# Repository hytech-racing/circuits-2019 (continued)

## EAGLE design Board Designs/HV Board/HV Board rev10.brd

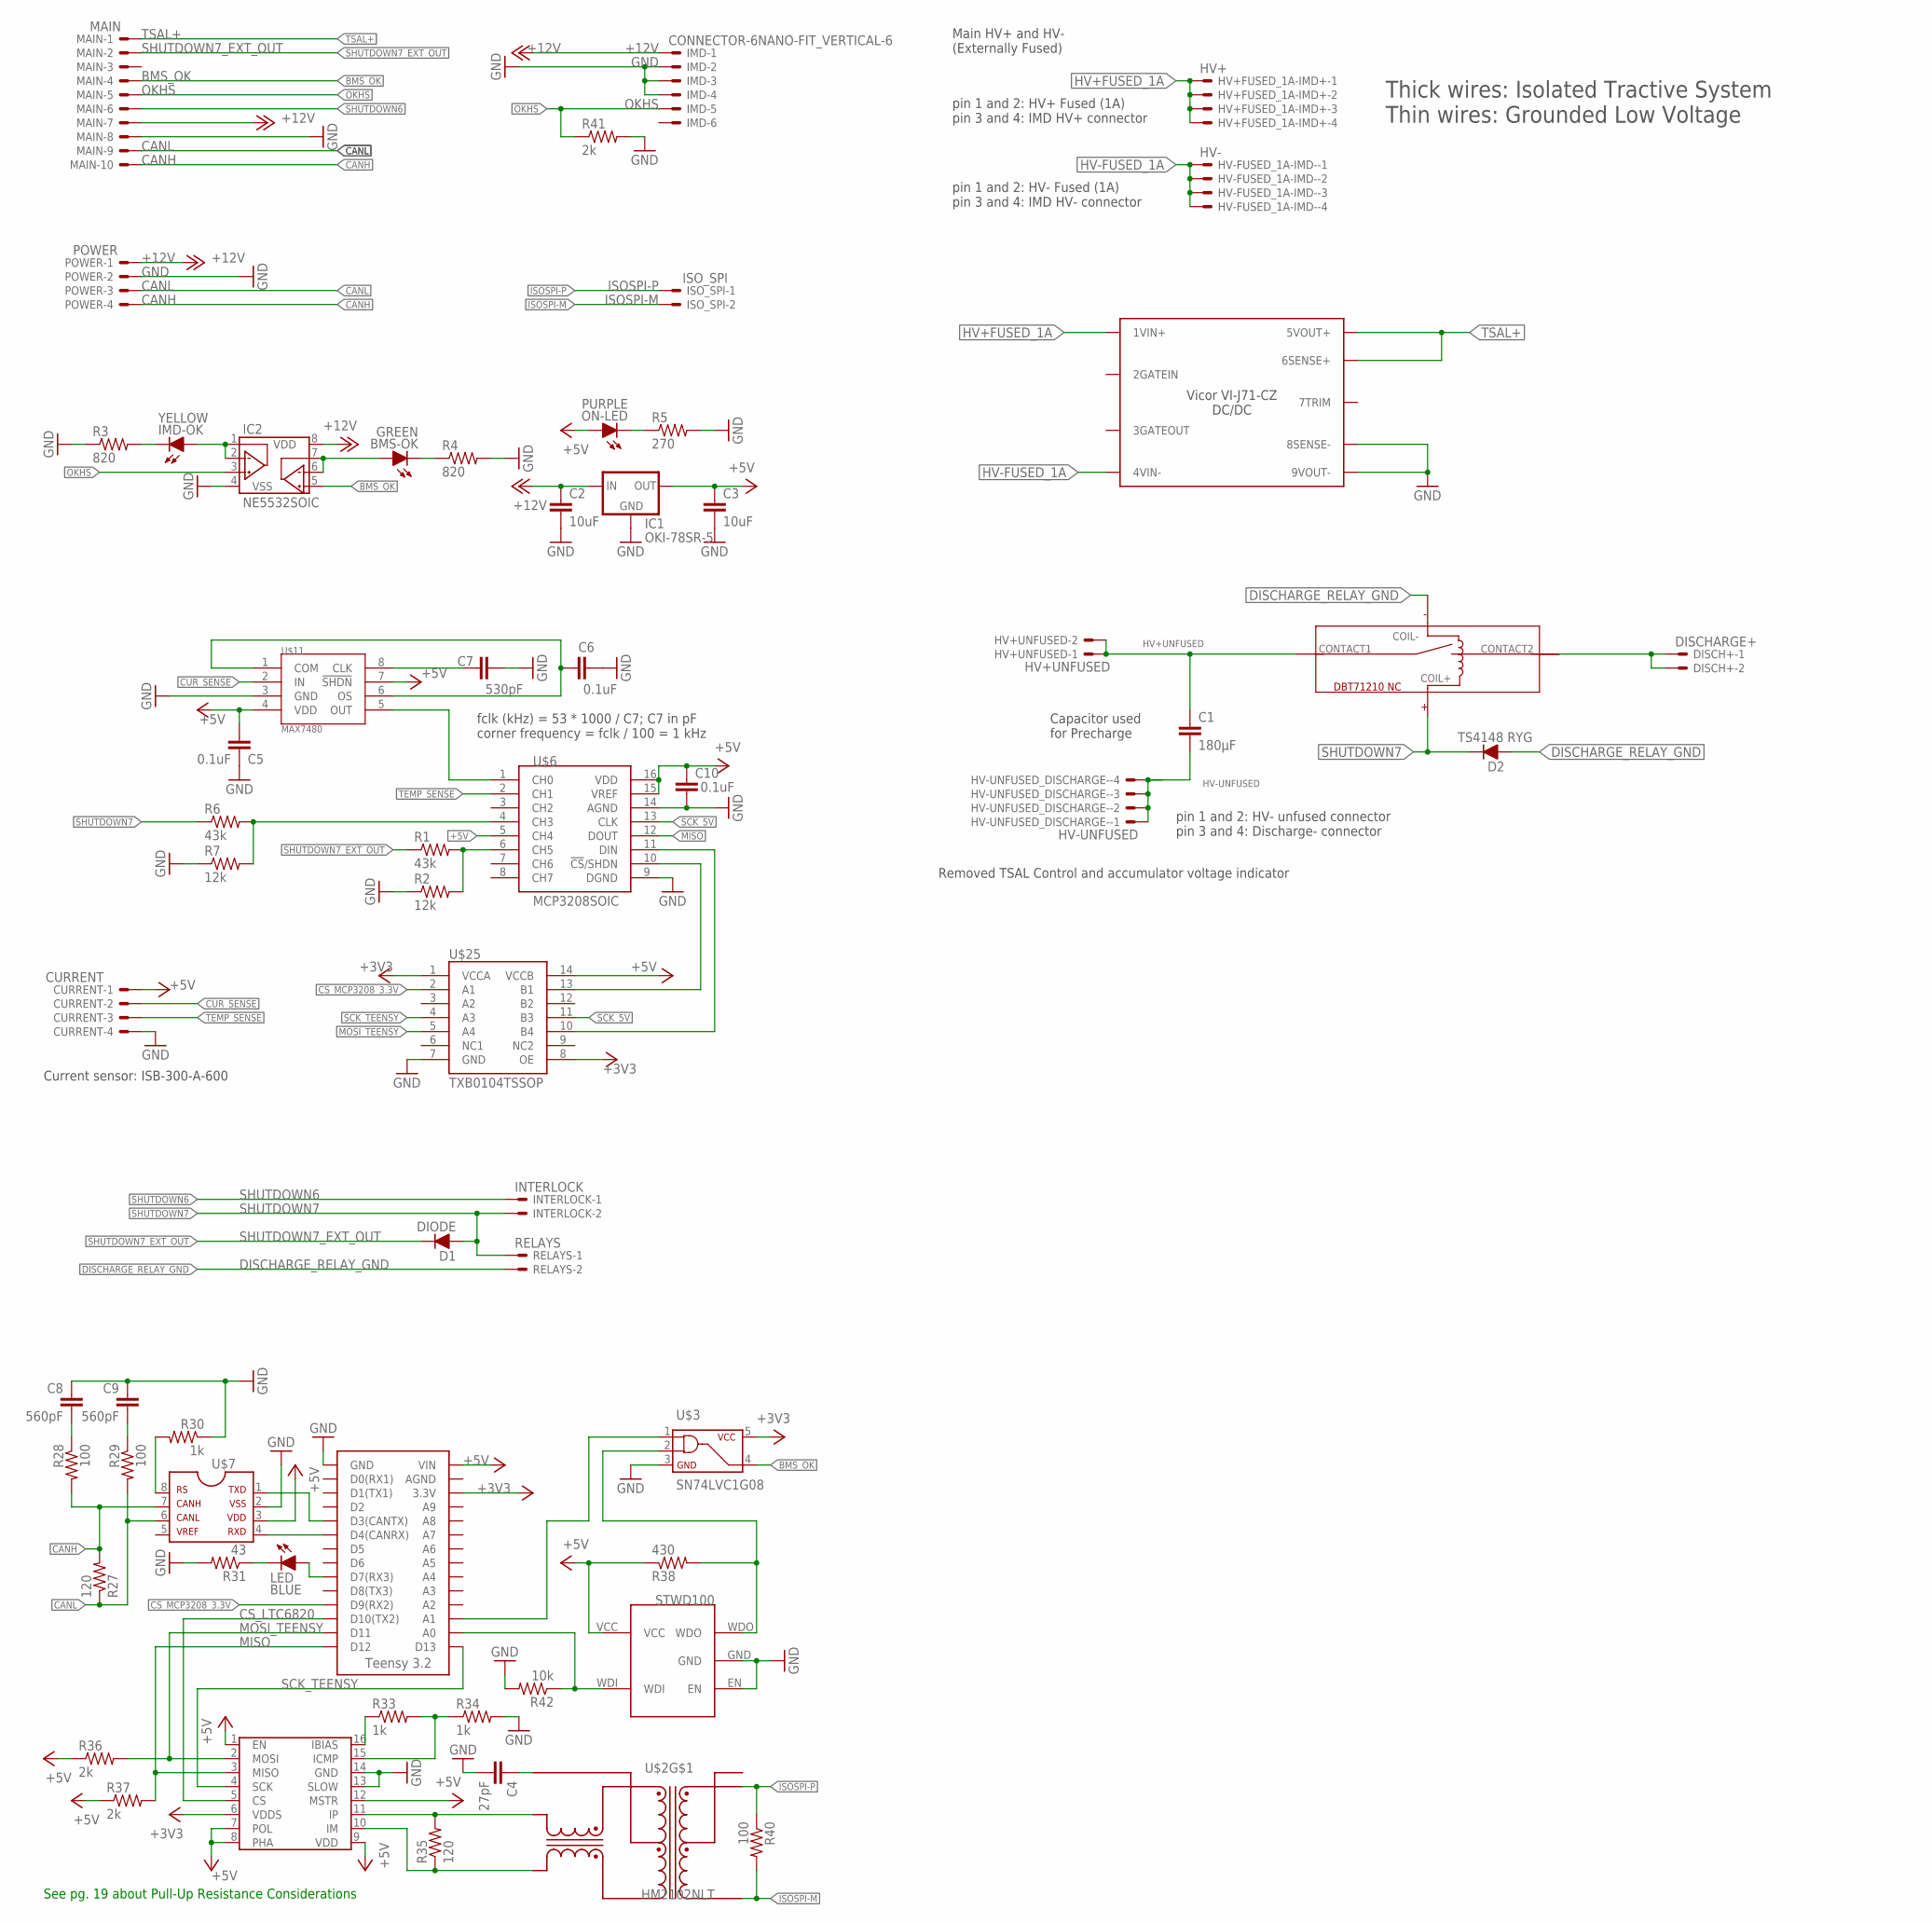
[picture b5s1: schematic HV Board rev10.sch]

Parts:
BMS-OK: GREEN; LED-805
C1: 180µF; LLS2V221MELZ
C2, C3: 10uF; 0805
C4: 27pF; 0805
C5, C6, C10: 0.1uF; 0805
C7: 530pF; 0805
C8, C9: 560pF; 0805
CURRENT: CURRENT; NANO-FIT_VERTICAL-4
D1: DIODE; DO-41
D2: TS4148 RYG; 0805_D
DISCH+: DISCHARGE+; NANO-FIT_VERTICAL-2
HV+FUSED_1A-IMD+: HV+; NANO-FIT_VERTICAL-4
HV+UNFUSED: HV+UNFUSED; NANO-FIT_VERTICAL-2
HV-FUSED_1A-IMD-: HV-; NANO-FIT_VERTICAL-4
HV-UNFUSED_DISCHARGE-: HV-UNFUSED; NANO-FIT_VERTICAL-4
IC1: OKI-78SR-5; OKI-78SR
IC2: NE5532SOIC; SOIC-08
IMD: CONNECTOR-6NANO-FIT_VERTICAL-6; NANO-FIT_VERTICAL-6
IMD-OK: YELLOW; LED-805
INTERLOCK: INTERLOCK; NANO-FIT_VERTICAL-2
ISO_SPI: ISO_SPI; NANO-FIT_VERTICAL-2
LED: BLUE; LED-805
MAIN: MAIN; NANO-FIT_VERTICAL-10
ON-LED: PURPLE; LED-805
POWER: POWER; NANO-FIT_VERTICAL-4
R1, R6: 43k; 0805
R2, R7: 12k; 0805
R3, R4: 820; 0805
R5: 270; 0805
R27, R35: 120; 0805
R28, R29, R40: 100; 0805
R30, R33, R34: 1k; 0805
R31: 43; 0805
R36, R37, R41: 2k; 0805
R38: 430; 0805
R42: 10k; 0805
RELAYS: RELAYS; NANO-FIT_VERTICAL-2
U$2: HM2102NLT
U$3: SN74LVC1G08; SOT-23-5
U$4: DBT71210
U$5: HV_DCDC_VI-J71-CZ
U$6: MCP3208SOIC; SOIC-16
U$7: MCP2551; SOIC-08
U$8: LTC6820; MSOP-16
U$9: TEENSY_3.2_SIMPLE
U$10: STWD100; SOT23-5
U$11: MAX7480; SOIC-08
U$25: TXB0104TSSOP; TSSOP-14

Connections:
+3V3: U$3.5, U$8.6 (VDDS), U$9.3.3V, U$25.1 (VCCA), U$25.8 (OE)
+5V: C3.1, C5.1, C10.1, CURRENT.P$1, IC1.3 (OUT), ON-LED.A, R36.1, R37.1, R38.1, U$6.5 (CH4), U$6.15 (VREF), U$6.16 (VDD), U$7.3, U$8.1 (EN), U$8.7 (POL), U$8.8 (PHA), U$8.9 (VDD), U$8.12 (MSTR), U$9.VIN, U$10.VCC, U$11.4 (VDD), U$25.14 (VCCB)
+12V: C2.1, IC1.1 (IN), IC2.8 (VDD), IMD.P$1, MAIN.P$7, POWER.P$1
BMS_OK: IC2.5 (VINB+), MAIN.P$4, U$3.4
CANH: MAIN.P$10, POWER.P$4, R27.2, R28.2, U$7.7
CANL: MAIN.P$9, POWER.P$3, R27.1, R29.2, U$7.6
CS_LTC6820: U$8.5 (CS), U$9.D10(TX2)
CS_MCP3208_3.3V: U$9.D9(RX2), U$25.2 (A1)
CUR_SENSE: CURRENT.P$2, U$11.2 (IN)
DISCHARGE_RELAY_GND: D2.A, RELAYS.P$2, U$4.COIL-
GND: C2.2, C3.2, C4.2, C5.2, C6.2, C7.2, C8.1, C9.1, C10.2, CURRENT.P$4, IC1.2 (GND), IC2.4 (VSS), IMD.P$2, IMD.P$3, IMD.P$4, MAIN.P$8, POWER.P$2, R2.1, R3.1, R4.2, R5.2, R7.1, R30.1, R31.2, R34.2, R41.2, R42.2, U$3.3, U$5.8SENSE-, U$5.9VOUT-, U$6.9 (DGND), U$6.14 (AGND), U$7.2, U$8.13 (SLOW), U$8.14 (GND), U$9.GND, U$10.EN, U$10.GND, U$11.3 (GND), U$25.7 (GND)
HV+FUSED_1A: HV+FUSED_1A-IMD+.P$1, HV+FUSED_1A-IMD+.P$2, HV+FUSED_1A-IMD+.P$3, HV+FUSED_1A-IMD+.P$4, U$5.1VIN+
HV+UNFUSED: C1.P$1 (1), HV+UNFUSED.P$1, HV+UNFUSED.P$2, U$4.CONTACT1
HV+UNFUSED_FSAE_DISCHARGE: DISCH+.P$1, DISCH+.P$2, U$4.CONTACT2
HV-FUSED_1A: HV-FUSED_1A-IMD-.P$1, HV-FUSED_1A-IMD-.P$2, HV-FUSED_1A-IMD-.P$3, HV-FUSED_1A-IMD-.P$4, U$5.4VIN-
HV-UNFUSED: C1.P$2 (2), HV-UNFUSED_DISCHARGE-.P$1, HV-UNFUSED_DISCHARGE-.P$2, HV-UNFUSED_DISCHARGE-.P$3, HV-UNFUSED_DISCHARGE-.P$4
IM: R35.1, U$2.P$10 (TD-), U$8.10 (IM)
IP: R35.2, U$2.P$12 (TD+), U$8.11 (IP)
ISOSPI-M: ISO_SPI.P$2, R40.2, U$2.P$3 (MX-)
ISOSPI-P: ISO_SPI.P$1, R40.1, U$2.P$1 (MX+)
MISO: R37.2, U$6.12 (DOUT), U$8.3 (MISO), U$9.D12
MOSI_5V: U$6.11 (DIN), U$25.10 (B4)
MOSI_TEENSY: R36.2, U$8.2 (MOSI), U$9.D11, U$25.5 (A4)
unnamed: U$6.1 (CH0), U$11.5 (OUT)
unnamed: C6.1, U$11.1 (COM), U$11.6 (OS)
unnamed: ON-LED.C, R5.1
unnamed: C7.1, U$11.8 (CLK)
unnamed: U$6.10 (!CS!/SHDN), U$25.13 (B1)
unnamed: R6.2, R7.2, U$6.4 (CH3)
unnamed: R1.2, R2.2, U$6.6 (CH5)
unnamed: U$7.1, U$9.D3(CANTX)
unnamed: R30.2, U$7.8
unnamed: C8.2, R28.1
unnamed: C9.2, R29.1
unnamed: LED.C, R31.1
unnamed: R33.1, U$8.16 (IBIAS)
unnamed: R33.2, R34.1, U$8.15 (ICMP)
unnamed: C4.1, U$2.P$11 (TCT)
unnamed: U$7.4, U$9.D4(CANRX)
unnamed: LED.A, U$9.D7(RX3)
unnamed: R38.2, U$3.2, U$10.WDO
unnamed: U$3.1, U$9.A1
unnamed: IC2.1 (VOUTA), IC2.2 (VINA-), IMD-OK.A
unnamed: BMS-OK.A, IC2.6 (VINB-), IC2.7 (VOUTB)
unnamed: BMS-OK.C, R4.1
unnamed: IMD-OK.C, R3.2
unnamed: R42.1, U$9.A0, U$10.WDI
OKHS: IC2.3 (VINA+), IMD.P$5, MAIN.P$5, R41.1
SCK_5V: U$6.13 (CLK), U$25.11 (B3)
SCK_TEENSY: U$8.4 (SCK), U$9.D13, U$25.4 (A3)
SHUTDOWN6: INTERLOCK.P$1, MAIN.P$6
SHUTDOWN7: D1.A, D2.C, INTERLOCK.P$2, R6.1, RELAYS.P$1, U$4.COIL+
SHUTDOWN7_EXT_OUT: D1.C, MAIN.P$2, R1.1
TEMP_SENSE: CURRENT.P$3, U$6.2 (CH1)
TSAL+: MAIN.P$1, U$5.5VOUT+, U$5.6SENSE+

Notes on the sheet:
Current sensor: ISB-300-A-600
Main HV+ and HV- (Externally Fused)
Thick wires: Isolated Tractive System Thin wires: Grounded Low Voltage
See pg. 19 about Pull-Up Resistance Considerations
Capacitor used for Precharge
Removed TSAL Control and accumulator voltage indicator
pin 1 and 2: HV+ Fused (1A) pin 3 and 4: IMD HV+ connector
pin 1 and 2: HV- Fused (1A) pin 3 and 4: IMD HV- connector
pin 1 and 2: HV- unfused connector pin 3 and 4: Discharge- connector
fclk (kHz) = 53 * 1000 / C7; C7 in pF corner frequency = fclk / 100 = 1 kHz

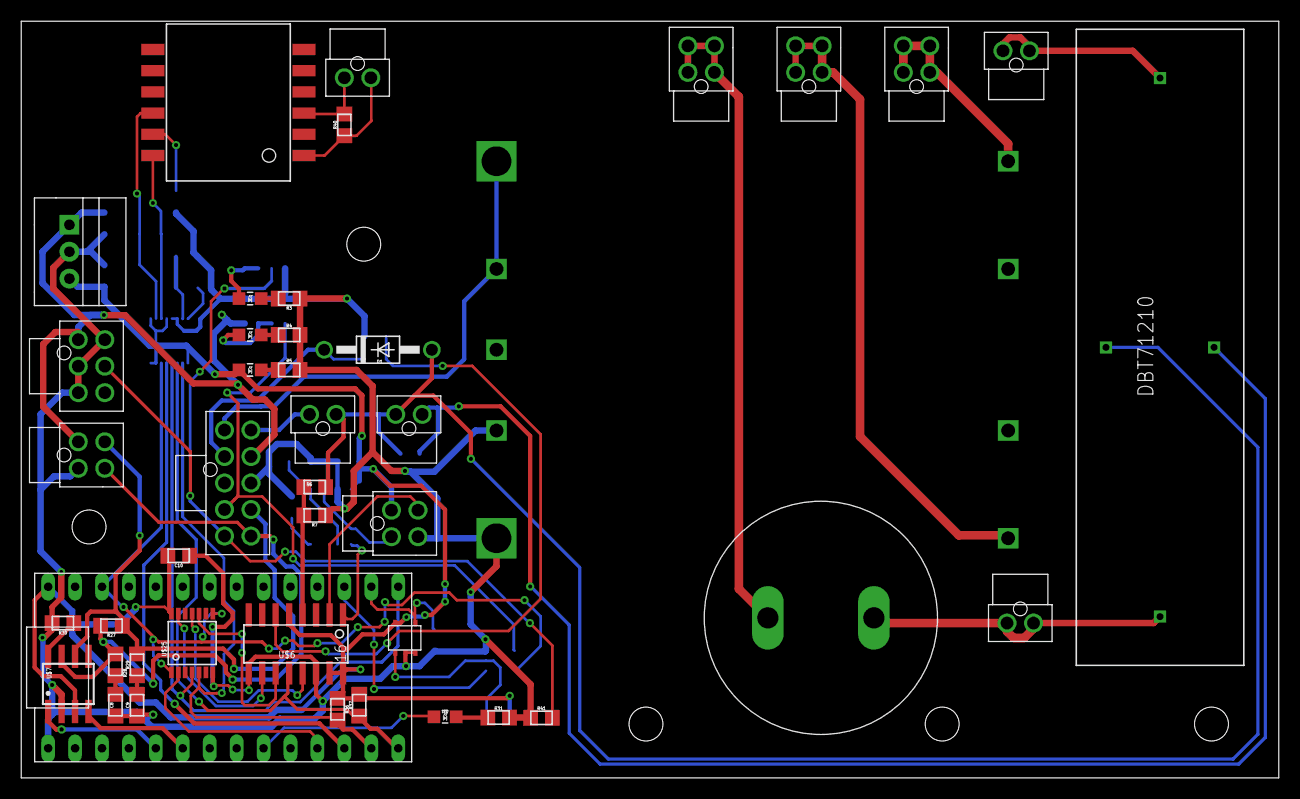
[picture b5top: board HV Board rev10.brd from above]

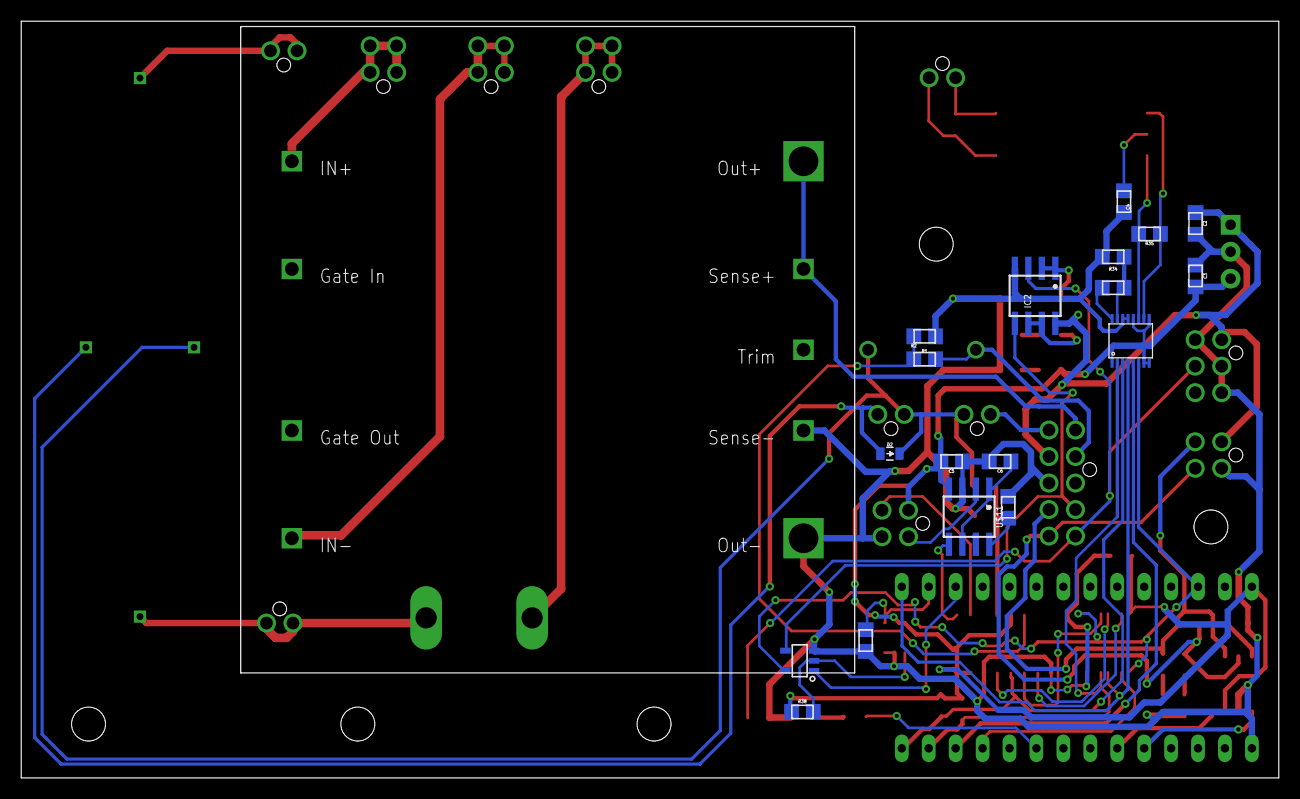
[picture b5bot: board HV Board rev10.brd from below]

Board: 2 copper layers, 118.6 x 71.4 mm, 62 parts (19 on the bottom side), 55 nets.

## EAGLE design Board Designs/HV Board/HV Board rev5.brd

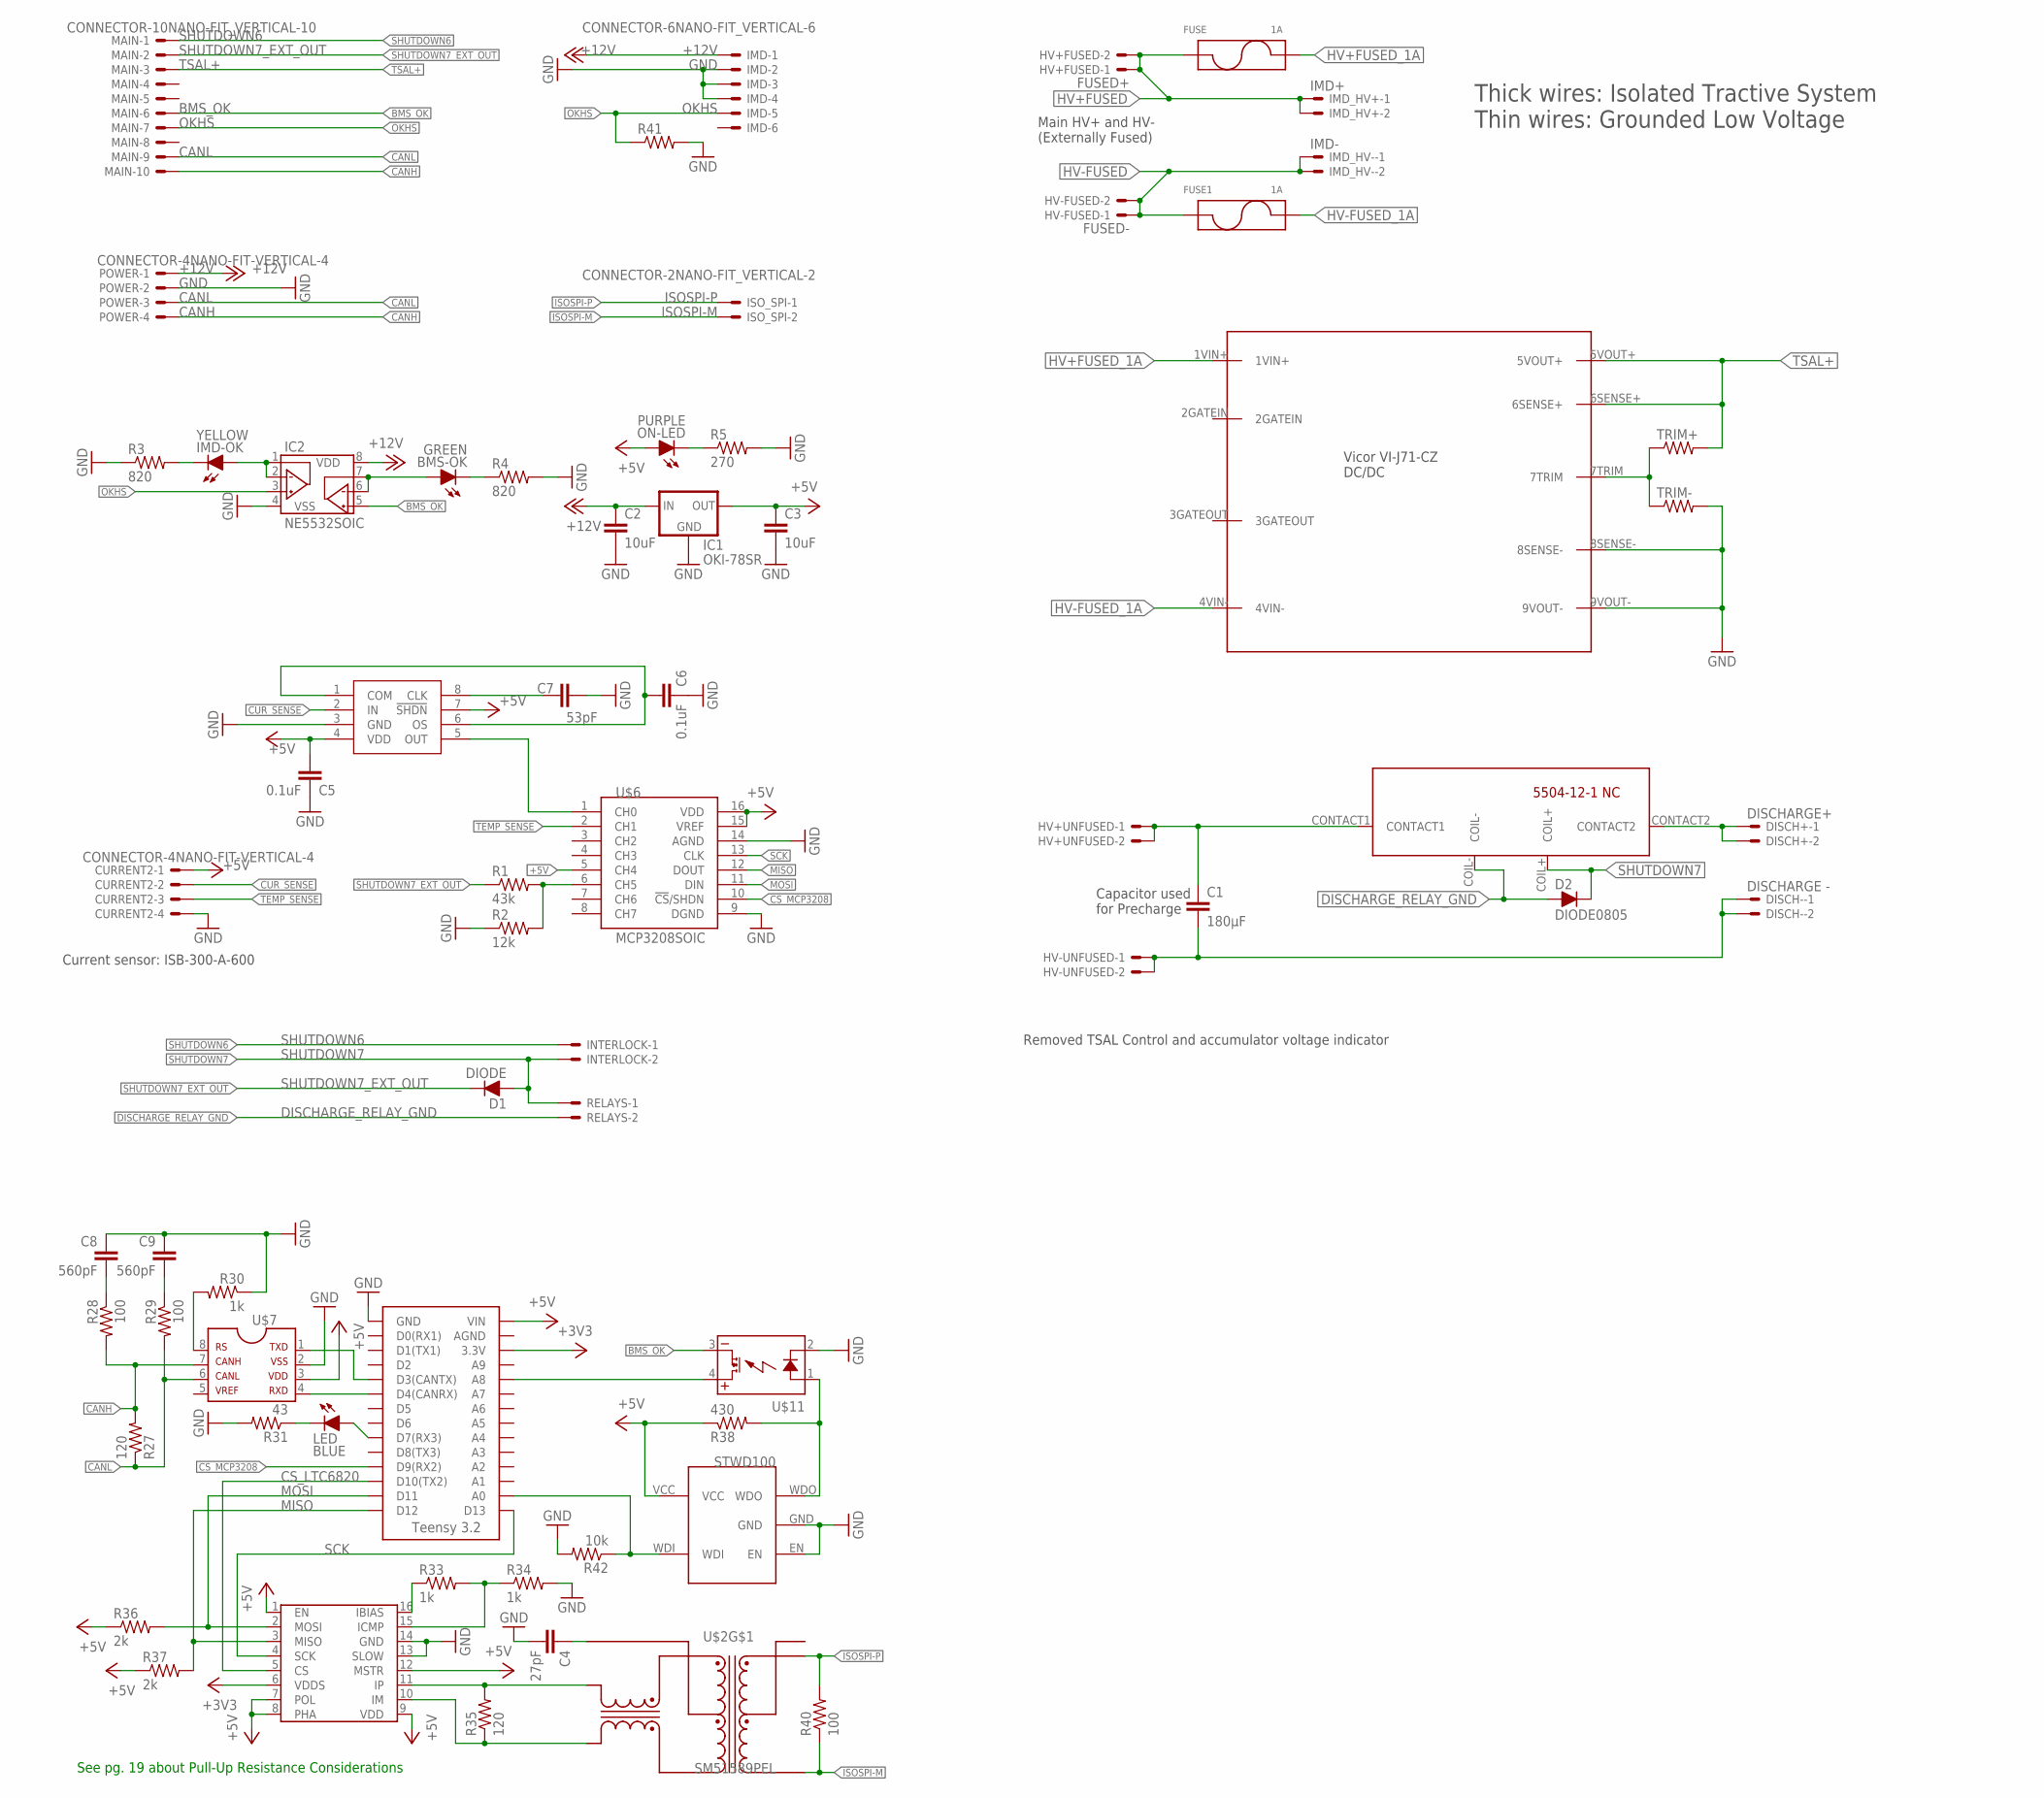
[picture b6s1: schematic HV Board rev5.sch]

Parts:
BMS-OK: GREEN; LED-805
C1: 180µF; LLS2V221MELZ
C2, C3: 10uF; 0805
C4: 27pF; 0805
C5, C6: 0.1uF; 0805
C7: 53pF; 0805
C8, C9: 560pF; 0805
CURRENT2: CONNECTOR-4NANO-FIT-VERTICAL-4; NANO-FIT_VERTICAL-4
D1: DIODE; DO-41
D2: DIODE0805; 0805_D
DISCH+: DISCHARGE+; MINIFIT_5566-2
DISCH-: DISCHARGE -; MINIFIT_5566-2
FUSE, FUSE1: 1A; 0751.0110
HV+FUSED: FUSED+; MINIFIT_5566-2
HV+UNFUSED: FSAE; MINIFIT_5566-2
HV-FUSED: FUSED-; MINIFIT_5566-2
HV-UNFUSED: HV_UNFUSED; MINIFIT_5566-2
IC1: OKI-78SR
IC2: NE5532SOIC; SOIC-08
IMD: CONNECTOR-6NANO-FIT_VERTICAL-6; NANO-FIT_VERTICAL-6
IMD-OK: YELLOW; LED-805
IMD_HV+: IMD+; MINIFIT_5566-2
IMD_HV-: IMD-; MINIFIT_5566-2
INTERLOCK: MINIFIT_5566-2
ISO_SPI: CONNECTOR-2NANO-FIT_VERTICAL-2; NANO-FIT_VERTICAL-2
LED: BLUE; LED-805
MAIN: CONNECTOR-10NANO-FIT_VERTICAL-10; NANO-FIT_VERTICAL-10
ON-LED: PURPLE; LED-805
POWER: CONNECTOR-4NANO-FIT-VERTICAL-4; NANO-FIT_VERTICAL-4
R1: 43k; 0805
R2: 12k; 0805
R3, R4: 820; 0805
R5: 270; 0805
R27, R35: 120; 0805
R28, R29, R40: 100; 0805
R30, R33, R34: 1k; 0805
R31: 43; 0805
R36, R37, R41: 2k; 0805
R38: 430; 0805
R42: 10k; 0805
RELAYS: MINIFIT_5566-2
TRIM+: RESISTOR0805-RES; 0805
TRIM-: RESISTOR0805-RES; 0805
U$1: MAX7480; SOIC-08
U$2: SM51589PEL
U$5: HV_DCDC_VI-J71-CZ
U$6: MCP3208SOIC; SOIC-16
U$7: MCP2551; SOIC-08
U$8: LTC6820; MSOP-16
U$9: TEENSY_3.2_SIMPLE
U$10: STWD100; SOT23-5
U$11: CPC1002N; SOP04
U$12: 5504-12-1-NC

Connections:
+3V3: U$8.6 (VDDS), U$9.3.3V
+5V: C3.1, C5.1, CURRENT2.P$1, IC1.3 (OUT), ON-LED.A, R36.1, R37.1, R38.1, U$1.4 (VDD), U$1.7 (!SHDN), U$6.5 (CH4), U$6.15 (VREF), U$6.16 (VDD), U$7.3, U$8.1 (EN), U$8.7 (POL), U$8.8 (PHA), U$8.9 (VDD), U$8.12 (MSTR), U$9.VIN, U$10.VCC
+12V: C2.1, IC1.1 (IN), IC2.8 (VDD), IMD.P$1, POWER.P$1
BMS_OK: IC2.5 (VINB+), MAIN.P$6, U$11.3 (DC-)
CANH: MAIN.P$10, POWER.P$4, R27.2, R28.2, U$7.7
CANL: MAIN.P$9, POWER.P$3, R27.1, R29.2, U$7.6
CS_LTC6820: U$8.5 (CS), U$9.D10(TX2)
CS_MCP3208: U$6.10 (!CS!/SHDN), U$9.D9(RX2)
CUR_SENSE: CURRENT2.P$2, U$1.2 (IN)
DISCHARGE_RELAY_GND: D2.A, RELAYS.2, U$12.COIL-
GND: C2.2, C3.2, C4.2, C5.2, C6.2, C7.2, C8.1, C9.1, CURRENT2.P$4, IC1.2 (GND), IC2.4 (VSS), IMD.P$2, IMD.P$3, IMD.P$4, POWER.P$2, R2.1, R3.1, R4.2, R5.2, R30.1, R31.2, R34.2, R41.2, R42.2, TRIM-.2, U$1.3 (GND), U$5.8SENSE-, U$5.9VOUT-, U$6.9 (DGND), U$6.14 (AGND), U$7.2, U$8.13 (SLOW), U$8.14 (GND), U$9.GND, U$10.EN, U$10.GND, U$11.2 (CONTROL-)
HV+FUSED: FUSE.L1 (P1), FUSE.L2 (P1), HV+FUSED.1, HV+FUSED.2, IMD_HV+.1, IMD_HV+.2
HV+FUSED_1A: FUSE.R1 (P2), FUSE.R2 (P2), U$5.1VIN+
HV+UNFUSED_FSAE: C1.P$1 (1), HV+UNFUSED.1, HV+UNFUSED.2, U$12.CONTACT1
HV+UNFUSED_FSAE_DISCHARGE: DISCH+.1, DISCH+.2, U$12.CONTACT2
HV-FUSED: FUSE1.L1 (P1), FUSE1.L2 (P1), HV-FUSED.1, HV-FUSED.2, IMD_HV-.1, IMD_HV-.2
HV-FUSED_1A: FUSE1.R1 (P2), FUSE1.R2 (P2), U$5.4VIN-
HV-UNFUSED_FSAE: C1.P$2 (2), DISCH-.1, DISCH-.2, HV-UNFUSED.1, HV-UNFUSED.2
ISOSPI-M: ISO_SPI.P$2, R40.1, U$2.3 (MX-)
ISOSPI-P: ISO_SPI.P$1, R40.2, U$2.2 (MX+)
MISO: R37.2, U$6.12 (DOUT), U$8.3 (MISO), U$9.D12
MOSI: R36.2, U$6.11 (DIN), U$8.2 (MOSI), U$9.D11
unnamed: U$1.5 (OUT), U$6.1 (CH0)
unnamed: C6.1, U$1.1 (COM), U$1.6 (OS)
unnamed: ON-LED.C, R5.1
unnamed: C7.1, U$1.8 (CLK)
unnamed: R1.2, R2.2, U$6.6 (CH5)
unnamed: U$7.1, U$9.D3(CANTX)
unnamed: R30.2, U$7.8
unnamed: C8.2, R28.1
unnamed: C9.2, R29.1
unnamed: LED.C, R31.1
unnamed: R33.1, U$8.16 (IBIAS)
unnamed: R33.2, R34.1, U$8.15 (ICMP)
unnamed: R35.1, U$2.22 (TD-), U$8.10 (IM)
unnamed: R35.2, U$2.23 (TD+), U$8.11 (IP)
unnamed: C4.1, U$2.24 (TCT)
unnamed: U$7.4, U$9.D4(CANRX)
unnamed: LED.A, U$9.D7(RX3)
unnamed: R38.2, U$10.WDO, U$11.1 (CONTROL+)
unnamed: U$9.A8, U$11.4 (DC+)
unnamed: IC2.1 (VOUTA), IC2.2 (VINA-), IMD-OK.A
unnamed: BMS-OK.A, IC2.6 (VINB-), IC2.7 (VOUTB)
unnamed: BMS-OK.C, R4.1
unnamed: IMD-OK.C, R3.2
unnamed: R42.1, U$9.A0, U$10.WDI
OKHS: IC2.3 (VINA+), IMD.P$5, MAIN.P$7, R41.1
SCK: U$6.13 (CLK), U$8.4 (SCK), U$9.D13
SHUTDOWN6: INTERLOCK.1, MAIN.P$1
SHUTDOWN7: D1.A, D2.C, INTERLOCK.2, RELAYS.1, U$12.COIL+
SHUTDOWN7_EXT_OUT: D1.C, MAIN.P$2, R1.1
TEMP_SENSE: CURRENT2.P$3, U$6.2 (CH1)
TRIM: TRIM+.1, TRIM-.1, U$5.7TRIM
TSAL+: MAIN.P$3, TRIM+.2, U$5.5VOUT+, U$5.6SENSE+

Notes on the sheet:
Current sensor: ISB-300-A-600
Main HV+ and HV- (Externally Fused)
Thick wires: Isolated Tractive System Thin wires: Grounded Low Voltage
See pg. 19 about Pull-Up Resistance Considerations
Capacitor used for Precharge
Removed TSAL Control and accumulator voltage indicator

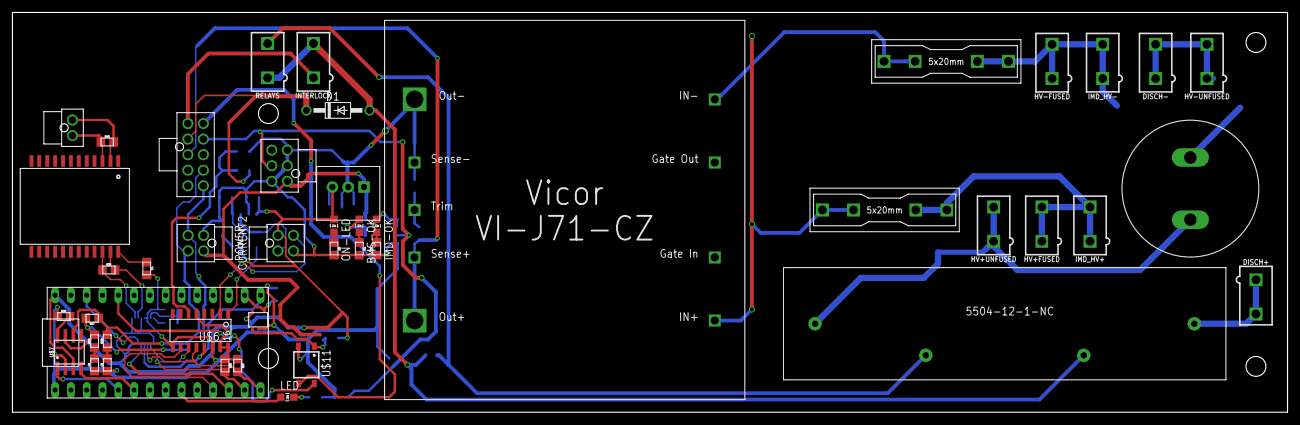
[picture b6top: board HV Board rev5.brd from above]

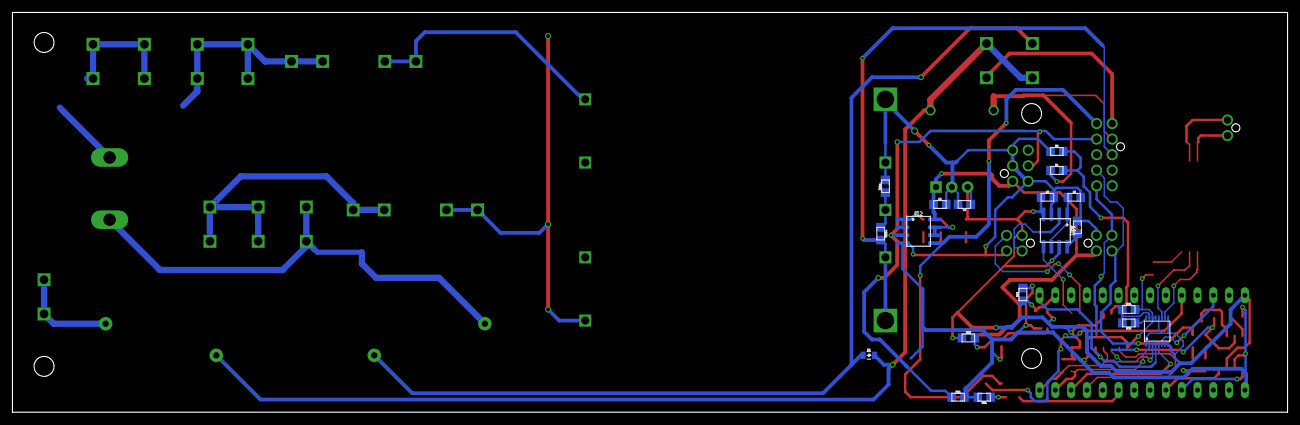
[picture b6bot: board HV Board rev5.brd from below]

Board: 2 copper layers, 205.0 x 64.3 mm, 65 parts (19 on the bottom side), 54 nets.
